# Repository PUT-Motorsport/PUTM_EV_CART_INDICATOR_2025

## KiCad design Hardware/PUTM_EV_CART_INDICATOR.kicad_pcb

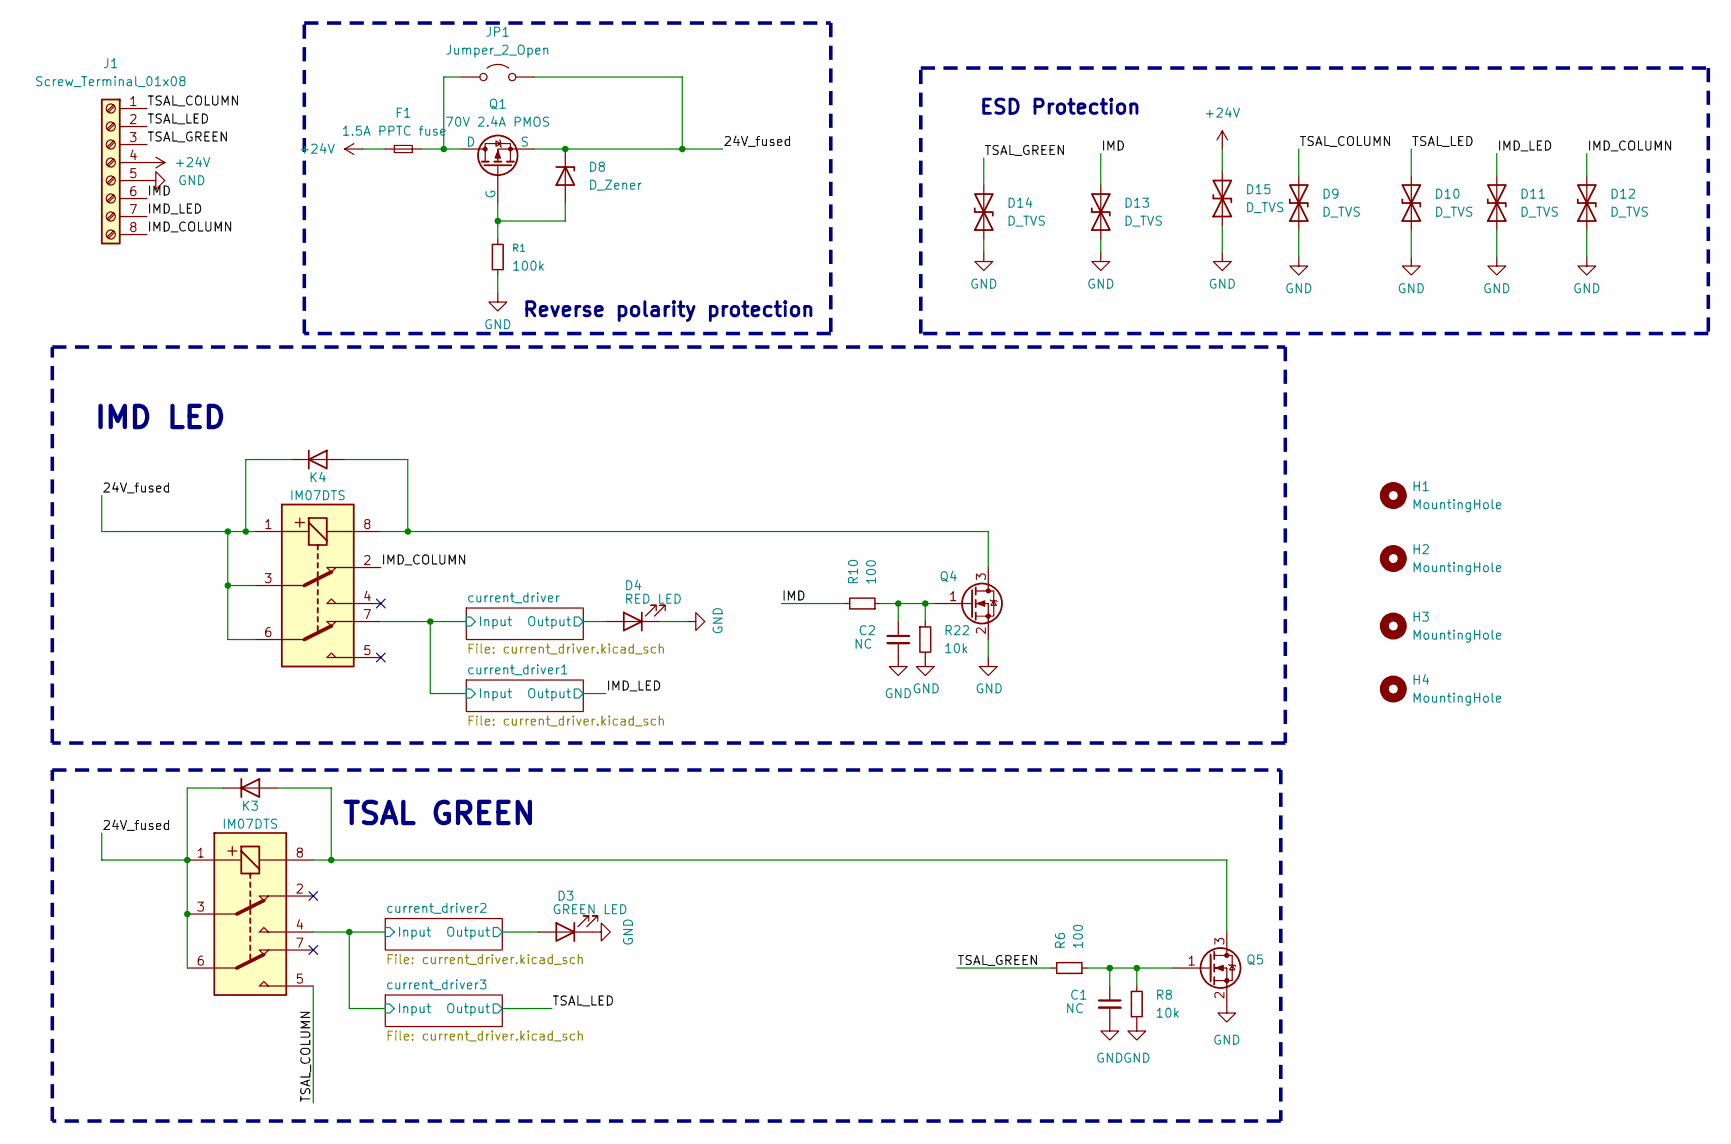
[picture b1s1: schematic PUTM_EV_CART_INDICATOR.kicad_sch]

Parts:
C1, C2: NC; C_0603_1608Metric_Pad1.08x0.95mm_HandSolder
D2, D6: D; Nexperia_CFP3_SOD-123W
D3: GREEN LED; LED_0603_1608Metric
D4: RED LED; LED_0603_1608Metric
D8: D_Zener; SODFL5026X125N
D9, D10, D11, D12, D13, D14, D15: D_TVS; SM4T82AY
F1: 1.5A PPTC fuse; Fuse_2920_7451Metric_Pad2.10x5.45mm_HandSolder
H1, H2, H3, H4: MountingHole; MountingHole_2.2mm_M2
J1: Screw_Terminal_01x08; TB00150008BE
JP1: Jumper_2_Open; SolderJumper-2_P1.3mm_Open_RoundedPad1.0x1.5mm
K3, K4: IM07DTS; IM23TS; Mouser Part Number 655-IM07DTS
Q1: 70V 2.4A PMOS; SOT-223
Q4, Q5: SOT-23
R1: 100k; R_0603_1608Metric_Pad0.98x0.95mm_HandSolder
R6, R10: 100; R_0603_1608Metric_Pad0.98x0.95mm_HandSolder; Manufacturer_Part_Number KDV08DR300ET; Mouser Part Number 588-KDV08DR300ET
R8: 10k; R_0603_1608Metric_Pad0.98x0.95mm_HandSolder; Manufacturer_Part_Number KDV08DR300ET; Mouser Part Number 588-KDV08DR300ET
R22: 10k; R_0603_1608Metric_Pad0.98x0.95mm_HandSolder

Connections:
+24V: D15.2 (A2), F1.2, J1.4
/24V_fused: D2.1 (K), D6.1 (K), D8.1 (K), JP1.2 (B), K3.1 (COIL_1), K3.3 (COM_1), K3.6 (COM_2), K4.1 (COIL_1), K4.3 (COM_1), K4.6 (COM_2), Q1.3 (S)
/IMD: D13.2 (A2), J1.6, R10.2
/IMD_COLUMN: D12.2 (A2), J1.8, K4.2 (NC_1)
/IMD_LED: D11.2 (A2), J1.7; also elsewhere on the board
/TSAL_COLUMN: D9.2 (A2), J1.1, K3.5 (NO_2)
/TSAL_GREEN: D14.2 (A2), J1.3, R6.2
/TSAL_LED: D10.2 (A2), J1.2; also elsewhere on the board
/current_driver2/Input: K3.4 (NO_1); also elsewhere on the board
/current_driver2/Output: D3.2 (A); also elsewhere on the board
/current_driver/Input: K4.7 (NC_2); also elsewhere on the board
/current_driver/Output: D4.2 (A); also elsewhere on the board
GND: C1.2, C2.2, D3.1 (K), D4.1 (K), D9.1 (A1), D10.1 (A1), D11.1 (A1), D12.1 (A1), D13.1 (A1), D14.1 (A1), D15.1 (A1), J1.5, Q4.2 (S), Q5.2 (S), R1.2, R8.1, R22.2
unnamed: D2.2 (A), K3.8 (COIL_2), Q5.3 (D)
unnamed: D6.2 (A), K4.8 (COIL_2), Q4.3 (D)
unnamed: D8.2 (A), Q1.1 (G), R1.1
unnamed: F1.1, JP1.1 (A), Q1.2 (D)
unnamed: C2.1, Q4.1 (G), R10.1, R22.1
unnamed: C1.1, Q5.1 (G), R6.1, R8.2

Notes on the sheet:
Reverse polarity protection
ESD Protection
TSAL GREEN
IMD LED

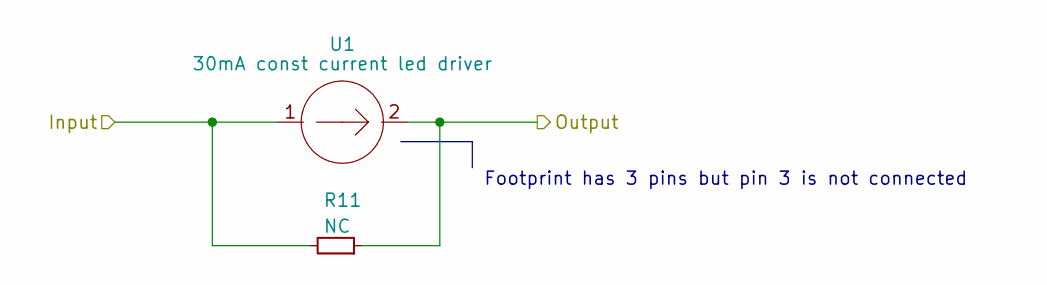
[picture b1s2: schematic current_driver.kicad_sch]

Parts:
R11: NC; R_0603_1608Metric_Pad0.98x0.95mm_HandSolder; Manufacturer_Part_Number KDV08DR300ET; Mouser Part Number 588-KDV08DR300ET
U1: 30mA const current led driver; D_PowerDI-123

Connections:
/current_driver/Input: R11.2, U1.1; also elsewhere on the board
/current_driver/Output: R11.1, U1.2; also elsewhere on the board

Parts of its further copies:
R13, R14, R15: NC; R_0603_1608Metric_Pad0.98x0.95mm_HandSolder; Manufacturer_Part_Number KDV08DR300ET; Mouser Part Number 588-KDV08DR300ET
U2, U3, U4: 30mA const current led driver; D_PowerDI-123

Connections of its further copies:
/IMD_LED: R13.1, U2.2; also elsewhere on the board
/TSAL_LED: R15.1, U4.2; also elsewhere on the board
/current_driver2/Input: R14.2, R15.2, U3.1, U4.1; also elsewhere on the board
/current_driver2/Output: R14.1, U3.2; also elsewhere on the board
/current_driver/Input: R13.2, U2.1; also elsewhere on the board

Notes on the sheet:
Footprint has 3 pins but pin 3 is not connected

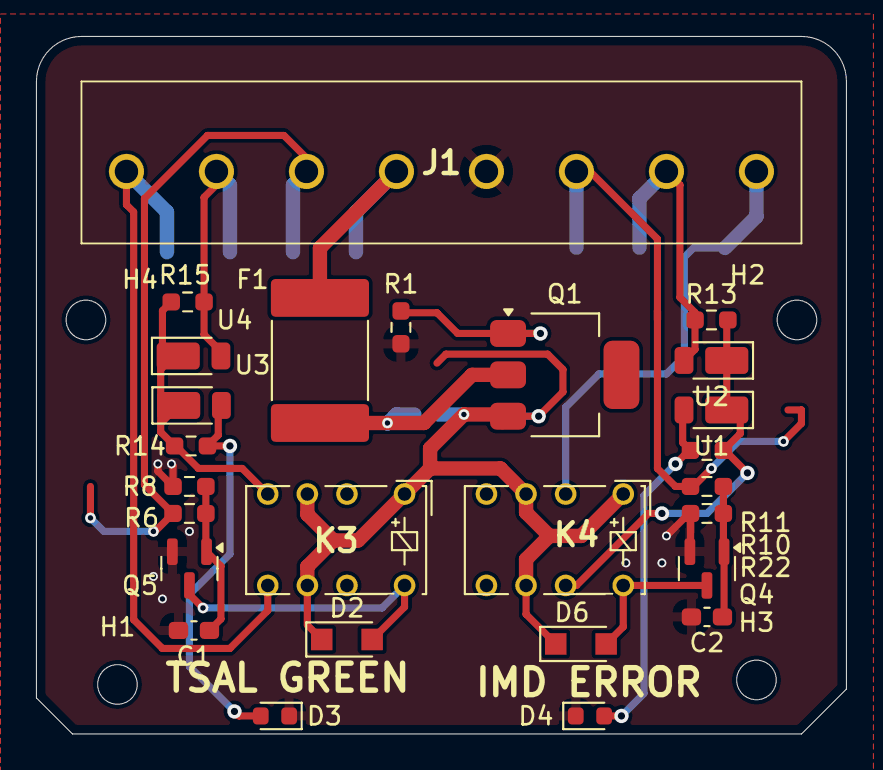
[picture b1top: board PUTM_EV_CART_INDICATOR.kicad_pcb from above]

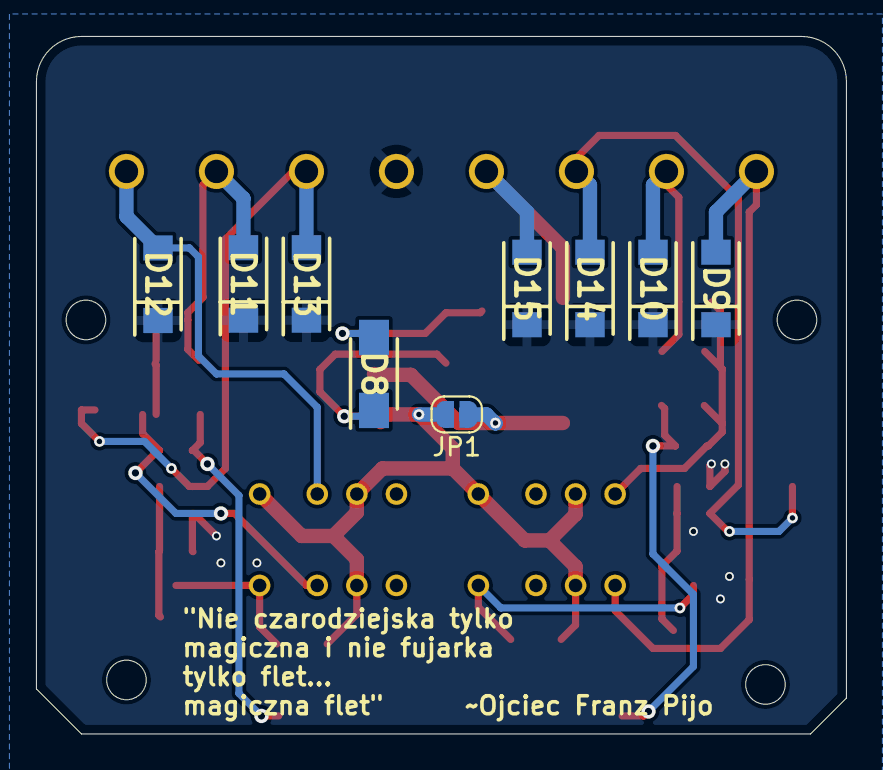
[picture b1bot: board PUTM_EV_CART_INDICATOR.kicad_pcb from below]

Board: 2 copper layers, 45.0 x 38.8 mm, 39 parts (9 on the bottom side), 19 nets.

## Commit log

2025-06-04 Pierwsza iteracja
2025-06-04 Zaktualizowano do standarow PUTM
2025-06-10 poprawy
2025-06-11 Zmieniono na przekaźniki
2025-06-11 dodano gerbery
2025-06-11 poprawa w forlderach
2025-06-14 poprawy diod
2025-06-14 melted tracks
2025-06-17 dodano otwory po drugiej stronie
2025-06-21 redy for relese 1.0
2025-09-17 Poprawiono schemat
2025-09-18 Wersja 2.0 do sprawdzenia :3
2025-09-18 Dodano esd protection, zmieniono komponenty, poprawiono schemat itp
2025-09-20 Dodano TVS na kazde wejscie, zmieniono diode w reverse polarity protection na zenera
